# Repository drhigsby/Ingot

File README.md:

# Ingot
 Ingot is a keyboard

KLE - http://www.keyboard-layout-editor.com/#/gists/b54f20879a48114b07ef3ab84a5364af

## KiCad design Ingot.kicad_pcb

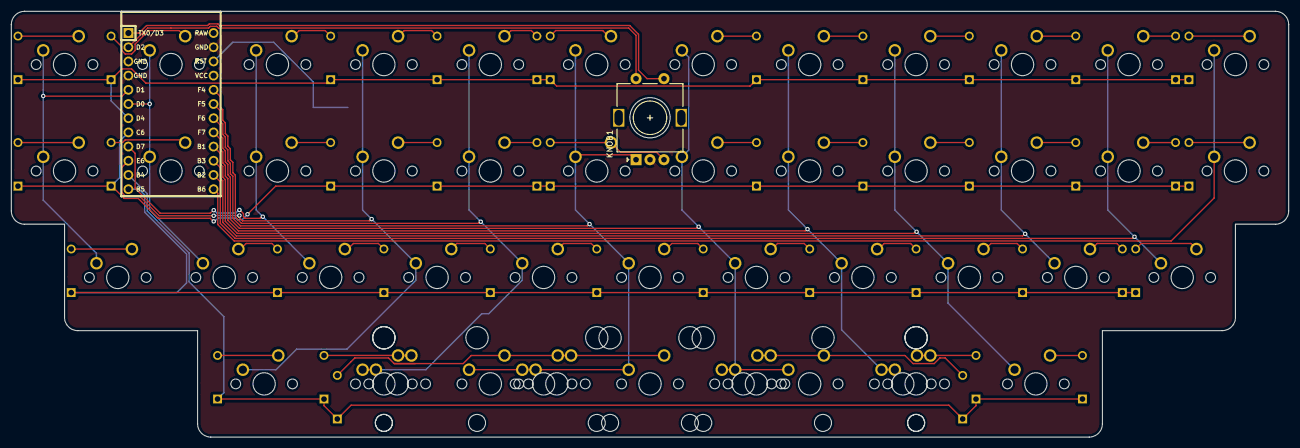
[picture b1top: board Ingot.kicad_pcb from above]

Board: 2 copper layers, 228.6 x 76.2 mm, 92 parts (1 on the bottom side), 61 nets.

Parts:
D1, D2, D3, D4, D5, D6, D7, D8, D9, D10, D11, D12, D13, D14, D15, D16, D17, D18, D19, D20, D21, D22, D23, D24, D25, D26, D27, D28, D29, D30, D31, D32, D33, D34, D35, D36, D37, D38, D39, D40, D41: D_Small; Diode-Hybrid-Back
KNOB1: Rotary_Encoder_Switch; RotaryEncoder_Alps_EC11E-Switch_Vertical_H20mm
MX1, MX2, MX3, MX4, MX5, MX6, MX7, MX8, MX9, MX10, MX11, MX12, MX13, MX14, MX15, MX16, MX17, MX18, MX19, MX20, MX21, MX22, MX23, MX24, MX25, MX26, MX27, MX28, MX29, MX30, MX31, MX32, MX33, MX34, MX35, MX37-1u1, MX40-1u1: MX-NoLED; MXOnly-1U-NoLED
MX36, MX37, MX40, MX41: MX-NoLED; MXOnly-1.25U-NoLED
MX38, MX39: MX-NoLED; MXOnly-1.75U-NoLED
MX38-2u1, MX39-2u1: MX-NoLED; MXOnly-2U-ReversedStabilizers-NoLED
MX38-3u1, MX39-3u1: MX-NoLED; MXOnly-3U-ReversedStabilizers-NoLED
MX38-6u1: MX-NoLED; MXOnly-6U-Centered-ReversedStabilizers-NoLED
PM1: ProMicro; ArduinoProMicro
RESET1: SW_Push; SW_SPST_SKQG_WithStem

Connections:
GND: KNOB1.C, PM1.3, PM1.4, PM1.23, RESET1.1
unnamed: D1.2, MX1.2
unnamed: D2.2, MX2.2
unnamed: D3.2, MX3.2
unnamed: D4.2, MX4.2
unnamed: D5.2, MX5.2
unnamed: D6.2, MX6.2
unnamed: D7.2, MX7.2
unnamed: D8.2, MX8.2
unnamed: D9.2, MX9.2
unnamed: D10.2, MX10.2
unnamed: D11.2, MX11.2
unnamed: D12.2, MX12.2
unnamed: D13.2, MX13.2
unnamed: D14.2, MX14.2
unnamed: D15.2, MX15.2
unnamed: D16.2, MX16.2
unnamed: D17.2, MX17.2
unnamed: D19.2, MX19.2
unnamed: D20.2, MX20.2
unnamed: D21.2, MX21.2
unnamed: D22.2, MX22.2
unnamed: D23.2, MX23.2
unnamed: D24.2, MX24.2
unnamed: D25.2, MX25.2
unnamed: D26.2, MX26.2
unnamed: D27.2, MX27.2
unnamed: D28.2, MX28.2
unnamed: D29.2, MX29.2
unnamed: D30.2, MX30.2
unnamed: D31.2, MX31.2
unnamed: D32.2, MX32.2
unnamed: D33.2, MX33.2
unnamed: D34.2, MX34.2
unnamed: D35.2, MX35.2
unnamed: D36.2, MX36.2
unnamed: D37.2, MX37.2, MX37-1u1.2
unnamed: D38.2, MX38.2, MX38-2u1.2, MX38-3u1.2, MX38-6u1.2
unnamed: D39.2, MX39.2, MX39-2u1.2, MX39-3u1.2
unnamed: D40.2, MX40.2, MX40-1u1.2
unnamed: D41.2, MX41.2
RST: PM1.22, RESET1.2
X1: KNOB1.S1, PM1.1
X2: KNOB1.S2, PM1.2
Z1: KNOB1.A, MX6.1, MX18.1, MX30.1, MX38.1, MX38-2u1.1, MX38-3u1.1, MX38-6u1.1, PM1.19
Z2: D18.2, KNOB1.B, MX18.2
c1: MX1.1, MX13.1, MX25.1, PM1.5
c2: MX2.1, MX14.1, MX26.1, PM1.6
c3: MX3.1, MX15.1, MX27.1, PM1.9
c4: MX4.1, MX16.1, MX28.1, MX36.1, PM1.10
c5: MX5.1, MX17.1, MX29.1, MX37.1, MX37-1u1.1, PM1.20
c7: MX7.1, MX19.1, MX31.1, MX39.1, MX39-2u1.1, MX39-3u1.1, PM1.18
c8: MX8.1, MX20.1, MX32.1, MX40.1, MX40-1u1.1, PM1.17
c9: MX9.1, MX21.1, MX33.1, MX41.1, PM1.16
c10: MX10.1, MX22.1, MX34.1, PM1.15
c11: MX11.1, MX23.1, MX35.1, PM1.14
c12: MX12.1, MX24.1, PM1.13
r1: D1.1, D2.1, D3.1, D4.1, D5.1, D6.1, D7.1, D8.1, D9.1, D10.1, D11.1, D12.1, PM1.7
r2: D13.1, D14.1, D15.1, D16.1, D17.1, D18.1, D19.1, D20.1, D21.1, D22.1, D23.1, D24.1, PM1.8
r3: D25.1, D26.1, D27.1, D28.1, D29.1, D30.1, D31.1, D32.1, D33.1, D34.1, D35.1, PM1.12
r4: D36.1, D37.1, D38.1, D39.1, D40.1, D41.1, PM1.11

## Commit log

2021-08-20 updated readme with kle
2021-08-20 fixed a few ladybug issues
